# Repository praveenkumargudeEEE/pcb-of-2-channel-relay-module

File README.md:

# pcb of 2 channel relay module in KICAD

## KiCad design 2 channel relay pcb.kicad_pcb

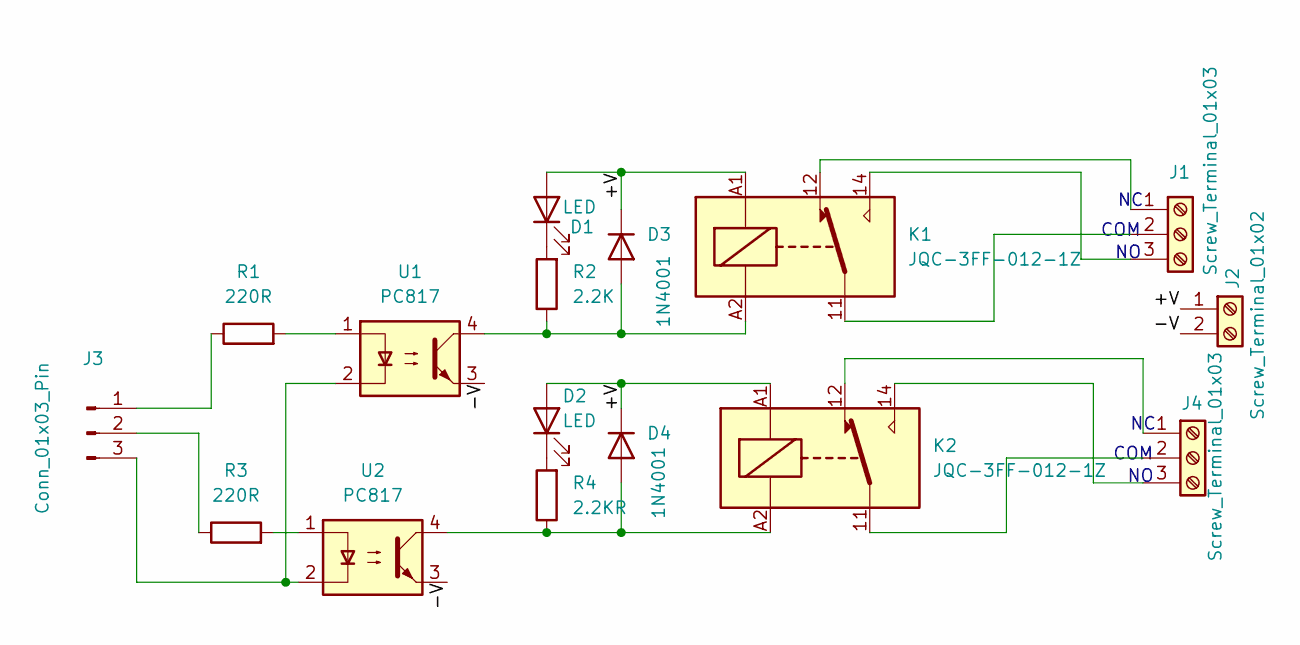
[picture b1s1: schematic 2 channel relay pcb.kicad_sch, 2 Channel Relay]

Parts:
D1, D2: LED; LED_0402_1005Metric
D3, D4: 1N4001; D_DO-41_SOD81_P10.16mm_Horizontal
J1, J4: Screw_Terminal_01x03; TerminalBlock_MaiXu_MX126-5.0-03P_1x03_P5.00mm
J2: Screw_Terminal_01x02; TerminalBlock_MaiXu_MX126-5.0-02P_1x02_P5.00mm
J3: Conn_01x03_Pin; PinHeader_1x03_P1.00mm_Horizontal
K1, K2: JQC-3FF-012-1Z; Relay_SPDT_Hongfa_JQC-3FF_0XX-1Z
R1, R3: 220R; R_0402_1005Metric
R2: 2.2K; R_0402_1005Metric
R4: 2.2KR; R_0402_1005Metric
U1, U2: PC817; DIP-4_W7.62mm

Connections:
/+V: D1.2 (A), D2.2 (A), D3.1 (K), D4.1 (K), J2.1, K1.A1, K2.A1
/-V: J2.2, U1.3, U2.3
unnamed: D1.1 (K), R2.2
unnamed: D2.1 (K), R4.2
unnamed: D3.2 (A), K1.A2, R2.1, U1.4
unnamed: D4.2 (A), K2.A2, R4.1, U2.4
unnamed: J1.1, K1.12
unnamed: J1.2, K1.11
unnamed: J1.3, K1.14
unnamed: J3.1, R1.1
unnamed: J3.2, R3.1
unnamed: J3.3, U1.2, U2.2
unnamed: J4.1, K2.12
unnamed: J4.2, K2.11
unnamed: J4.3, K2.14
unnamed: R1.2, U1.1
unnamed: R3.2, U2.1

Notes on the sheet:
COM

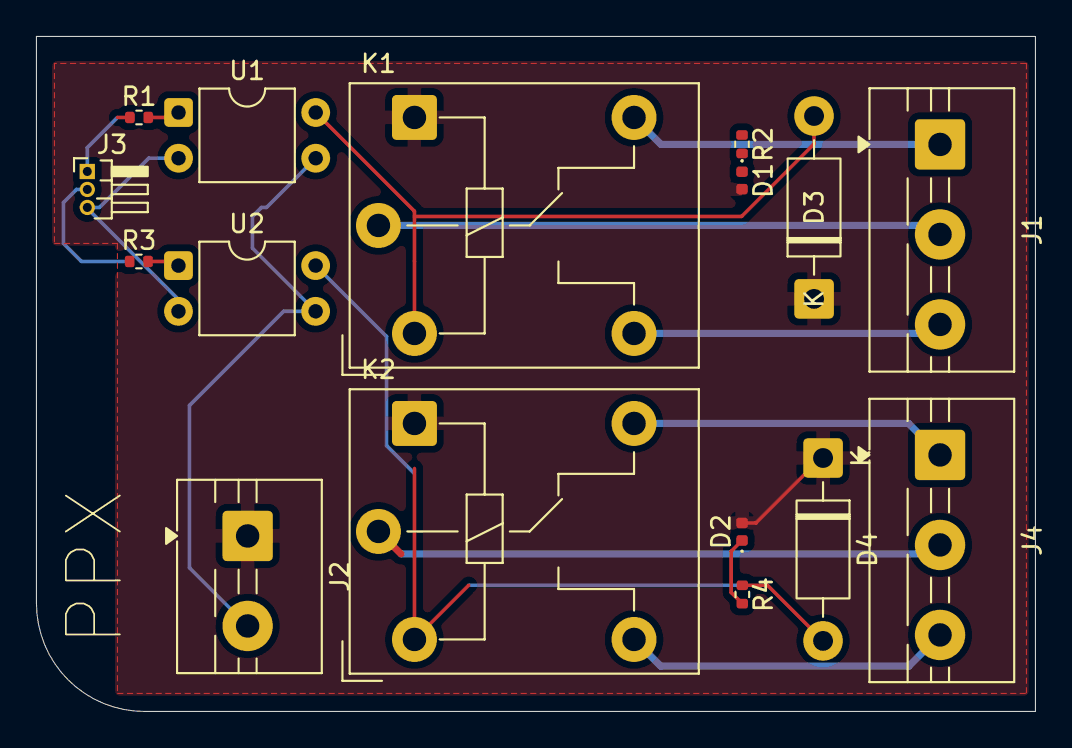
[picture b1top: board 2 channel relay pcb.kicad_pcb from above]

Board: 2 copper layers, 55.5 x 37.5 mm, 16 parts (0 on the bottom side), 17 nets.
